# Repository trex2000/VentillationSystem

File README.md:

# VentillationSystem
VentillationSystem

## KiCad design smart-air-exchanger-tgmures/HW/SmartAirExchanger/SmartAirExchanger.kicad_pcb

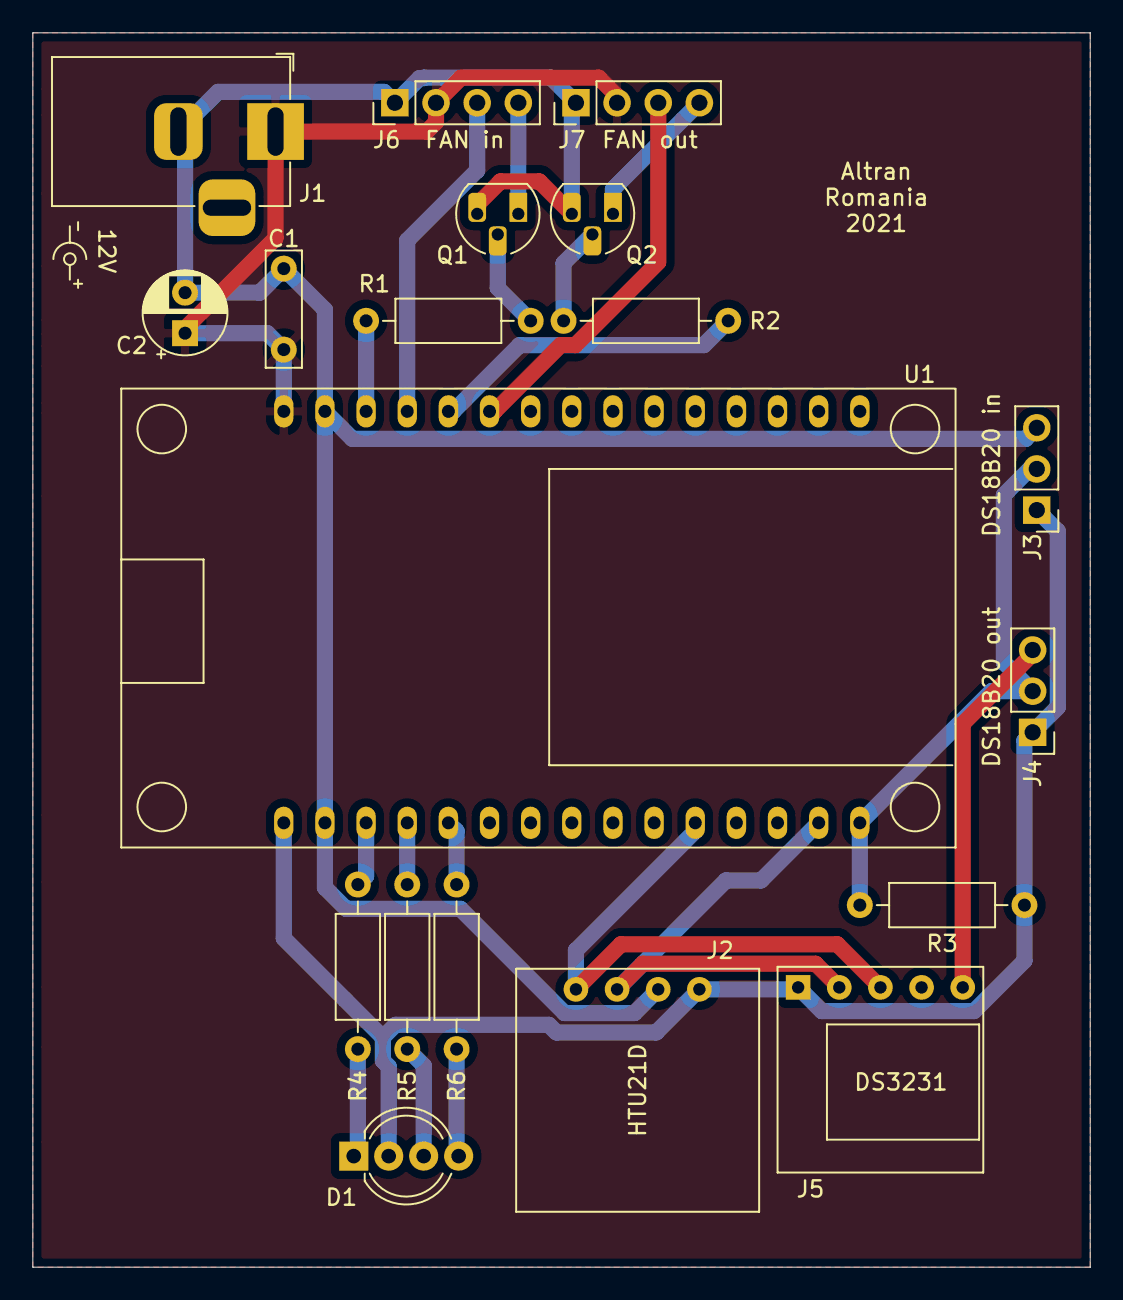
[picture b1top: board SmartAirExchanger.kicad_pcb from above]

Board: 2 copper layers, 65.3 x 76.2 mm, 19 parts (0 on the bottom side), 20 nets.

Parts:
C1: 100n; C_Rect_L7.0mm_W2.0mm_P5.00mm
C2: 10u/50V; CP_Radial_D5.0mm_P2.50mm
D1: LED_RAGB; LED_D5.0mm-4_RGB_Wide_Pins
J1: PWR; BarrelJack_Horizontal
J2: Humidity_sensor; HTU21D_board
J3: Temp_sensor_IN; PinHeader_1x03_P2.54mm_Vertical
J4: Temp_sensor_OUT; PinHeader_1x03_P2.54mm_Vertical
J5: RTC; RTC_DS3231_board
J6: Fan_IN; PinHeader_1x04_P2.54mm_Vertical
J7: Fan_OUT; PinHeader_1x04_P2.54mm_Vertical
Q1, Q2: BC547; TO-92_HandSolder
R1, R2: 10k; R_Axial_DIN0207_L6.3mm_D2.5mm_P10.16mm_Horizontal
R3: 4k7; R_Axial_DIN0207_L6.3mm_D2.5mm_P10.16mm_Horizontal
R4, R5, R6: 1k; R_Axial_DIN0207_L6.3mm_D2.5mm_P10.16mm_Horizontal
U1: ESP32_DEVKIT_V1

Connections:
+3V3: D1.2, J2.1, J3.1, J4.1, J5.1, R3.1, U1.1
+12V: C1.1, C2.1, J1.1, J6.2, J7.2, U1.30
/SCL: J2.4, J5.3, U1.11
/SDA: J2.3, J5.2, U1.14
GND: C1.2, C2.2, J1.2, J2.2, J3.3, J4.3, J5.5, J6.1, J7.1, Q1.3, Q2.3, U1.2, U1.29
unnamed: D1.1, R4.1
unnamed: D1.3, R5.1
unnamed: D1.4, R6.1
unnamed: J3.2, J4.2, R3.2, U1.15
unnamed: J6.3, U1.27
unnamed: J6.4, Q1.1
unnamed: J7.3, U1.25
unnamed: J7.4, Q2.1
unnamed: Q1.2, R1.1
unnamed: Q2.2, R2.1
unnamed: R1.2, U1.28
unnamed: R2.2, U1.26
unnamed: R4.2, U1.3
unnamed: R5.2, U1.4
unnamed: R6.2, U1.5

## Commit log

2023-10-17 Migrated from Gitlab
2023-10-17 Added Schematic and Lucrarea de Licenta encrypted
2023-10-23 Added Req. Specification
2023-10-23 Added coding guideline document
